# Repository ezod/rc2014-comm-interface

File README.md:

# RC2014 Communication Interface Module

This is a serial communication module for [RC2014](https://rc2014.co.uk/) computers providing an easy way to switch dual serial port connections between RS232, FTDI, and an ESP01 module.

| Switch Position | Port A | Port B |
|-----------------|--------|--------|
| left            | FTDI   | ESP01  |
| middle          | RS232  | ESP01  |
| right           | RS232  | FTDI   |

These configuration options allow you to switch between a PC and a serial terminal as the main console, connect either to an ESP01 modem using [Zimodem](https://github.com/bozimmerman/Zimodem) or similar, and do XMODEM transfers over FTDI from a serial terminal.

## Bill of Materials

| Reference | Part                             |
|-----------|----------------------------------|
|     U1    | LD1117V33                        |
|     U2    | MAX232N                          |
|   U3-U4   | CD4053B                          |
|   R1-R6   | 1K resistor                      |
|     R7    | 3.3K resistor                    |
|     R8    | 4.7K resistor                    |
|   R9-R10  | 10K resistor                     |
|   C1-C4   | 1uF electrolytic capacitor       |
|   C5-C6   | 10uF electrolytic capacitor      |
|     C7    | 47uF electrolytic capacitor      |
|   C8-C10  | 0.1uF disc/MLCC capacitor        |
|     S1    | EG2315 DP3T slide switch         |
|     S2    | right angle tactile switch       |
|     J1    | 1x6 0.1" right angle pin header  |
|     J2    | DE9 female socket                |
|     J3    | 2x8 0.1" straight pin socket     |
|    JP1    | 1x2 0.1" straight pin header     |
|    BUS    | 2x40 0.1" right angle pin header |

For the DE9 socket (J2), use [NorComp 182-009-213R561](https://www.digikey.ca/en/products/detail/norcomp-inc/182-009-213R561/1120101) or similar.

This module optionally connects RTS signals to the RS232 and FTDI connectors. If you are using the [Dual Serial Module SIO/2](https://rc2014.co.uk/modules/dual-serial-module-sio2/), to use the RTS signals, you will need to bodge pin 17 (RTSA) of U3 to pin 37 (SPARE1) of the bus, and pin 24 (RTSB) of U3 to pin 38 (SPARE2) of the bus. Otherwise, you can leave R5 and R6 unpopulated.

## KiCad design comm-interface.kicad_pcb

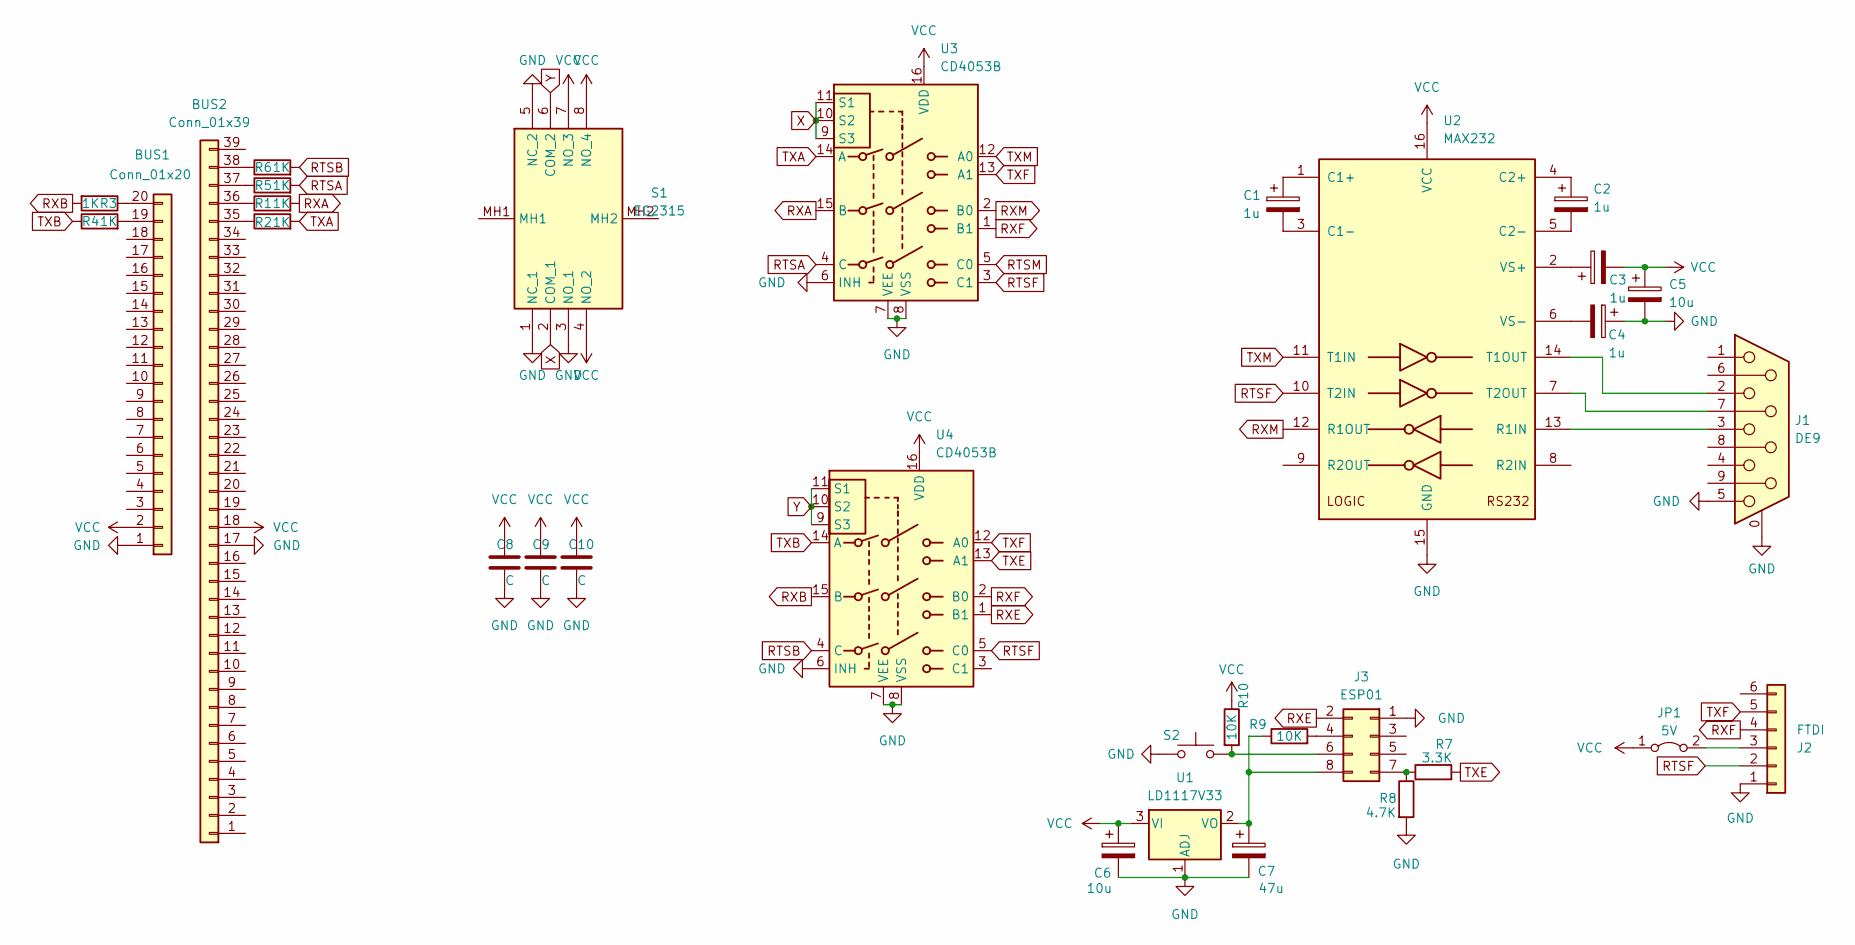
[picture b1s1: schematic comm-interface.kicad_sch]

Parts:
BUS1: Conn_01x20; PinHeader_1x20_P2.54mm_Vertical
BUS2: Conn_01x39; PinHeader_1x39_P2.54mm_Vertical
C1, C2, C3, C4: 1u; CP_Radial_D4.0mm_P2.00mm
C5, C6: 10u; CP_Radial_D5.0mm_P2.50mm
C7: 47u; CP_Radial_D5.0mm_P2.50mm
C8, C9, C10: C; C_Disc_D5.0mm_W2.5mm_P2.50mm
J1: DE9; DSUB-9_Female_Horizontal_P2.77x2.84mm_EdgePinOffset7.70mm_H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
J2: FTDI; PinHeader_1x06_P2.54mm_Horizontal
J3: ESP01; PinSocket_2x04_P2.54mm_Vertical
JP1: 5V; PinHeader_1x02_P2.54mm_Vertical
R1, R2, R3, R4, R5, R6: 1K; R_Axial_DIN0207_L6.3mm_D2.5mm_P10.16mm_Horizontal
R7: 3.3K; R_Axial_DIN0207_L6.3mm_D2.5mm_P10.16mm_Horizontal
R8: 4.7K; R_Axial_DIN0207_L6.3mm_D2.5mm_P10.16mm_Horizontal
R9, R10: 10K; R_Axial_DIN0207_L6.3mm_D2.5mm_P10.16mm_Horizontal
S1: EG2315; Mouser Part Number 612-EG2315
S2: SW_Push; SW_Tactile_SPST_Angled_PTS645Vx39-2LFS
U1: LD1117V33; TO-220-3_Horizontal_TabDown
U2: MAX232; DIP-16_W7.62mm_Socket
U3, U4: CD4053B; DIP-16_W7.62mm_Socket

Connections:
GND: BUS1.1, BUS2.17, C4.1, C5.2, C6.2, C7.2, C8.2, C9.2, C10.2, J1.0 (PAD), J1.5, J2.1, J3.1, R8.2, S1.1 (NC_1), S1.3 (NO_1), S1.5 (NC_2), S2.1, U1.1 (ADJ), U2.15 (GND), U3.6 (INH), U3.7 (VEE), U3.8 (VSS), U4.6 (INH), U4.7 (VEE), U4.8 (VSS)
unnamed: BUS1.19, R4.2
unnamed: BUS1.20, R3.1
unnamed: BUS2.35, R2.1
unnamed: BUS2.36, R1.1
unnamed: BUS2.37, R5.1
unnamed: BUS2.38, R6.1
unnamed: J2.3, JP1.2 (B)
unnamed: J3.4, R9.2
unnamed: J3.6, R10.2, S2.2
unnamed: J3.7, R7.1, R8.1
unnamed: C7.1, J3.8, R9.1, U1.2 (VO)
unnamed: C1.1, U2.1 (C1+)
unnamed: C1.2, U2.3 (C1-)
unnamed: C2.1, U2.4 (C2+)
unnamed: C2.2, U2.5 (C2-)
unnamed: J1.3, U2.13 (R1IN)
unnamed: J1.2, U2.14 (T1OUT)
unnamed: J1.7, U2.7 (T2OUT)
unnamed: C3.1, U2.2 (VS+)
unnamed: C4.2, U2.6 (VS-)
RTSA: R5.2, U3.4 (C)
RTSB: R6.2, U4.4 (C)
RTSF: J2.2, U2.10 (T2IN), U3.3 (C1), U4.5 (C0)
RTSM: U3.5 (C0)
RXA: R1.2, U3.15 (B)
RXB: R3.2, U4.15 (B)
RXE: J3.2, U4.1 (B1)
RXF: J2.4, U3.1 (B1), U4.2 (B0)
RXM: U2.12 (R1OUT), U3.2 (B0)
TXA: R2.2, U3.14 (A)
TXB: R4.1, U4.14 (A)
TXE: R7.2, U4.13 (A1)
TXF: J2.5, U3.13 (A1), U4.12 (A0)
TXM: U2.11 (T1IN), U3.12 (A0)
VCC: BUS1.2, BUS2.18, C3.2, C5.1, C6.1, C8.1, C9.1, C10.1, JP1.1 (A), R10.1, S1.4 (NO_2), S1.7 (NO_3), S1.8 (NO_4), U1.3 (VI), U2.16 (VCC), U3.16 (VDD), U4.16 (VDD)
X: S1.2 (COM_1), U3.9 (S3), U3.10 (S2), U3.11 (S1)
Y: S1.6 (COM_2), U4.9 (S3), U4.10 (S2), U4.11 (S1)

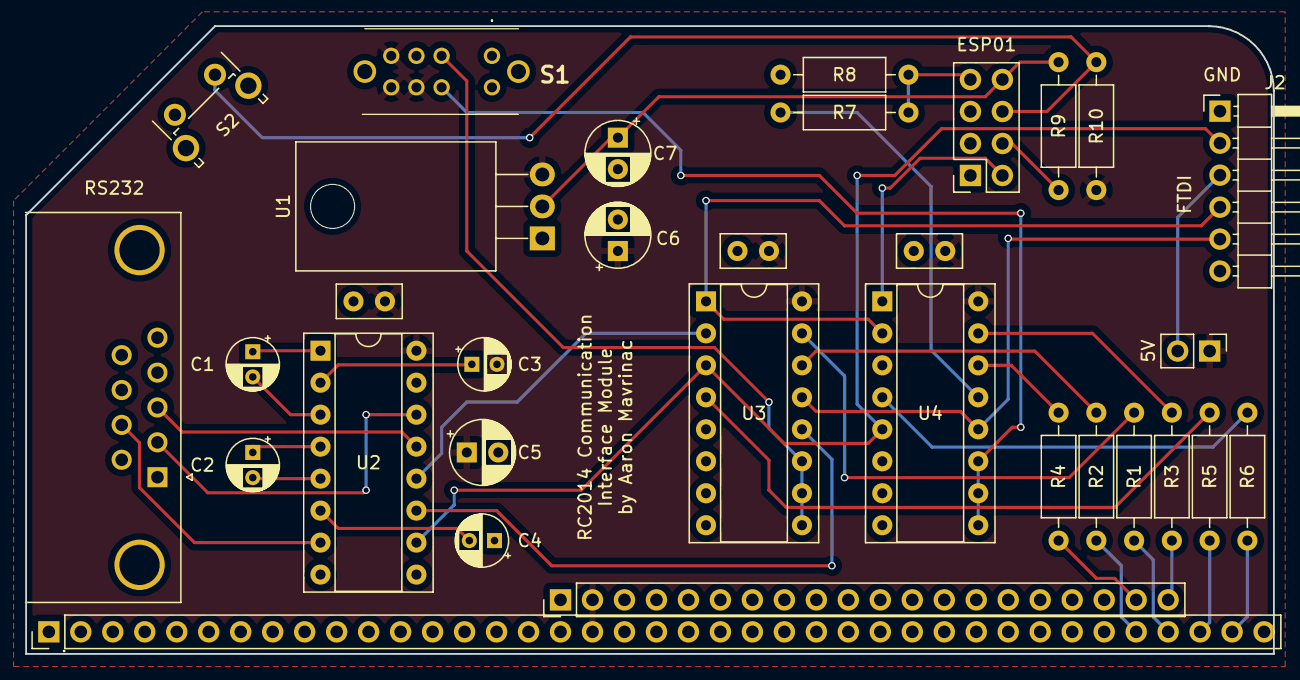
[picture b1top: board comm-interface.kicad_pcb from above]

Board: 2 copper layers, 99.1 x 49.9 mm, 32 parts (0 on the bottom side), 37 nets.

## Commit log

2025-06-25 Initial import of KiCad project and gerbers.
2025-06-25 Add README.
2025-06-25 Crop PCB image.
